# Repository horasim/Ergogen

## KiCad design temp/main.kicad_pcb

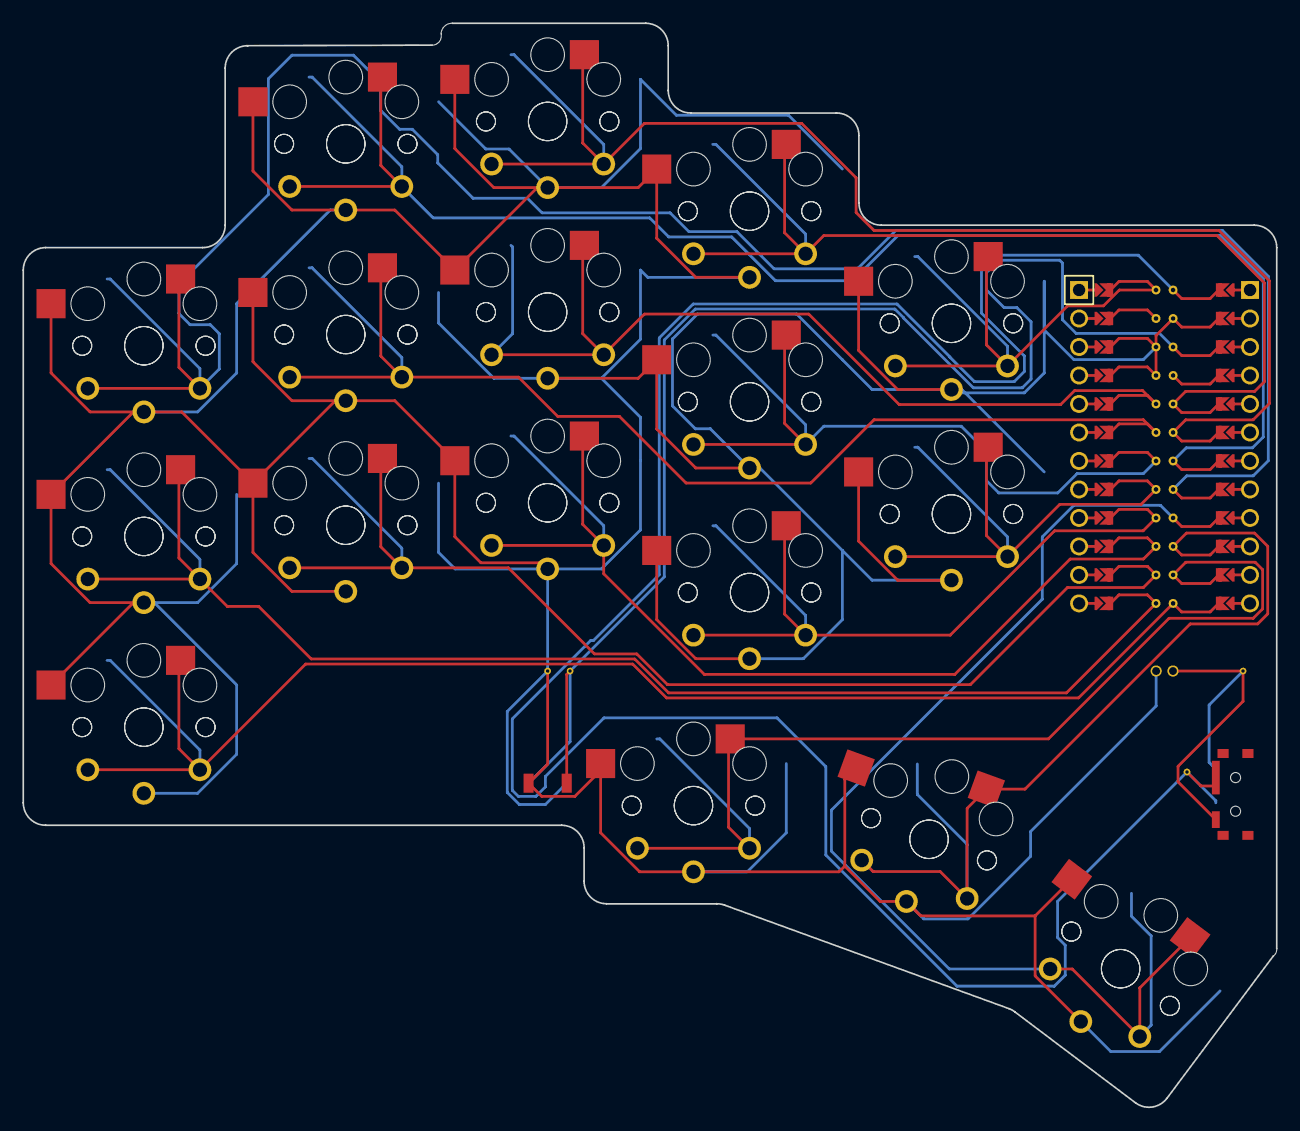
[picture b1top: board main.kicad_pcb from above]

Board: 2 copper layers, 111.8 x 96.6 mm, 35 parts (0 on the bottom side), 18 nets.

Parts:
MCU1: ProMicro
S1, S2, S3, S4, S5, S6, S7, S8, S9, S10, S11, S12, S13, S14, S15, S16, S17, S18, S19, S20, S21, S22, S23, S24, S25, S26, S27, S28, S29, S30, S31, S32, S33, S34: PG1350

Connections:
GND: MCU1.2, MCU1.21, MCU1.22, S1.2, S2.2, S3.2, S4.2, S5.2, S6.2, S7.2, S8.2, S9.2, S10.2, S11.2, S12.2, S13.2, S14.2, S15.2, S16.2, S17.2, S18.2, S19.2, S20.2, S21.2, S22.2, S23.2, S24.2, S25.2, S26.2, S27.2, S28.2, S29.2, S30.2, S31.2, S32.2, S33.2, S34.2
P1: MCU1.24, S27.1, S28.1
P2: MCU1.20, S15.1, S16.1
P3: MCU1.19, S9.1, S10.1
P4: MCU1.18, S21.1, S22.1
P5: MCU1.17, S25.1, S26.1
P6: MCU1.16, S19.1, S20.1
P7: MCU1.15, S13.1, S14.1
P8: MCU1.14, S7.1, S8.1
P9: MCU1.13, S3.1, S4.1
P10: MCU1.12, S1.1, S2.1
P14: MCU1.10, S31.1, S32.1
P15: MCU1.9, S33.1, S34.1
P16: MCU1.11, S29.1, S30.1
P18: MCU1.8, S5.1, S6.1
P19: MCU1.7, S11.1, S12.1
P20: MCU1.6, S17.1, S18.1
P21: MCU1.5, S23.1, S24.1

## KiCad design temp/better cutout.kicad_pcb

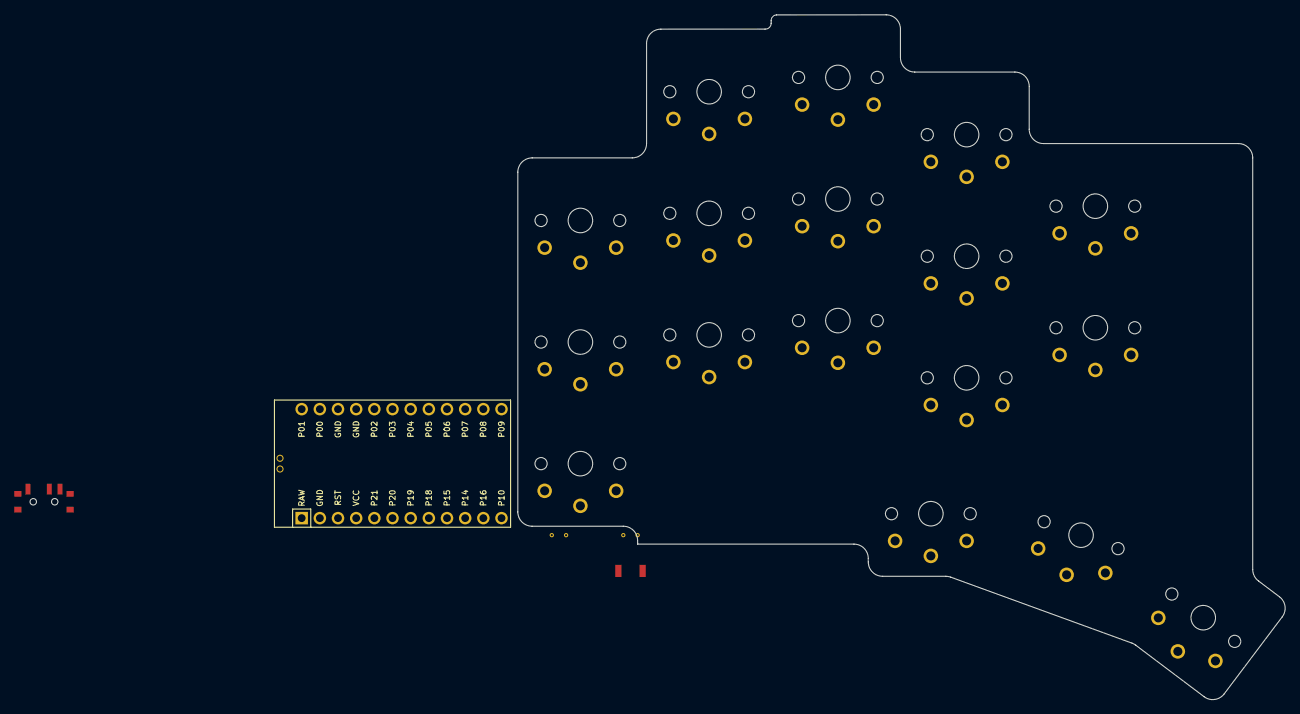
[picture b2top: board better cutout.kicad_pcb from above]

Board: 2 copper layers, 107.3 x 95.7 mm, 18 parts (0 on the bottom side), 11 nets, no tracks yet.

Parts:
MCU1: ProMicro
S1, S2, S3, S4, S5, S6, S7, S8, S9, S10, S11, S12, S13, S14, S15, S16, S17: PG1350

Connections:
GND: MCU1.2, MCU1.15, MCU1.16, S1.2, S2.2, S3.2, S4.2, S5.2, S6.2, S7.2, S8.2, S9.2, S10.2, S11.2, S12.2, S13.2, S14.2, S15.2, S16.2, S17.2
P1: MCU1.13, S17.1
P2: MCU1.17, S16.1
P3: MCU1.18, S15.1
P4: MCU1.19, S13.1
P5: MCU1.20, S14.1
P6: MCU1.21, S12.1
P7: MCU1.22, S11.1
P8: MCU1.23, S3.1, S6.1, S9.1
P9: MCU1.24, S5.1, S8.1
P10: MCU1.12, S2.1, S4.1, S7.1, S10.1

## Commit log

2022-05-27 Updated node
2022-05-27 Added my config and KiCAD output
2022-05-30 temp moved to basic directory added gerber files
2022-06-03 added main.kicad
